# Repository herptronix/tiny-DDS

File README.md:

Tiny DDS
================

Open source (hardware & software) DDS generator, based on:
 - smart TFT module
 - AD9834
 - LM7171 fast amplifier

Small video: https://www.youtube.com/watch?v=Hllg0D2UqWg
Some explanations (french only): http://herptronix.blogspot.fr/2014/08/tiny-dds.html

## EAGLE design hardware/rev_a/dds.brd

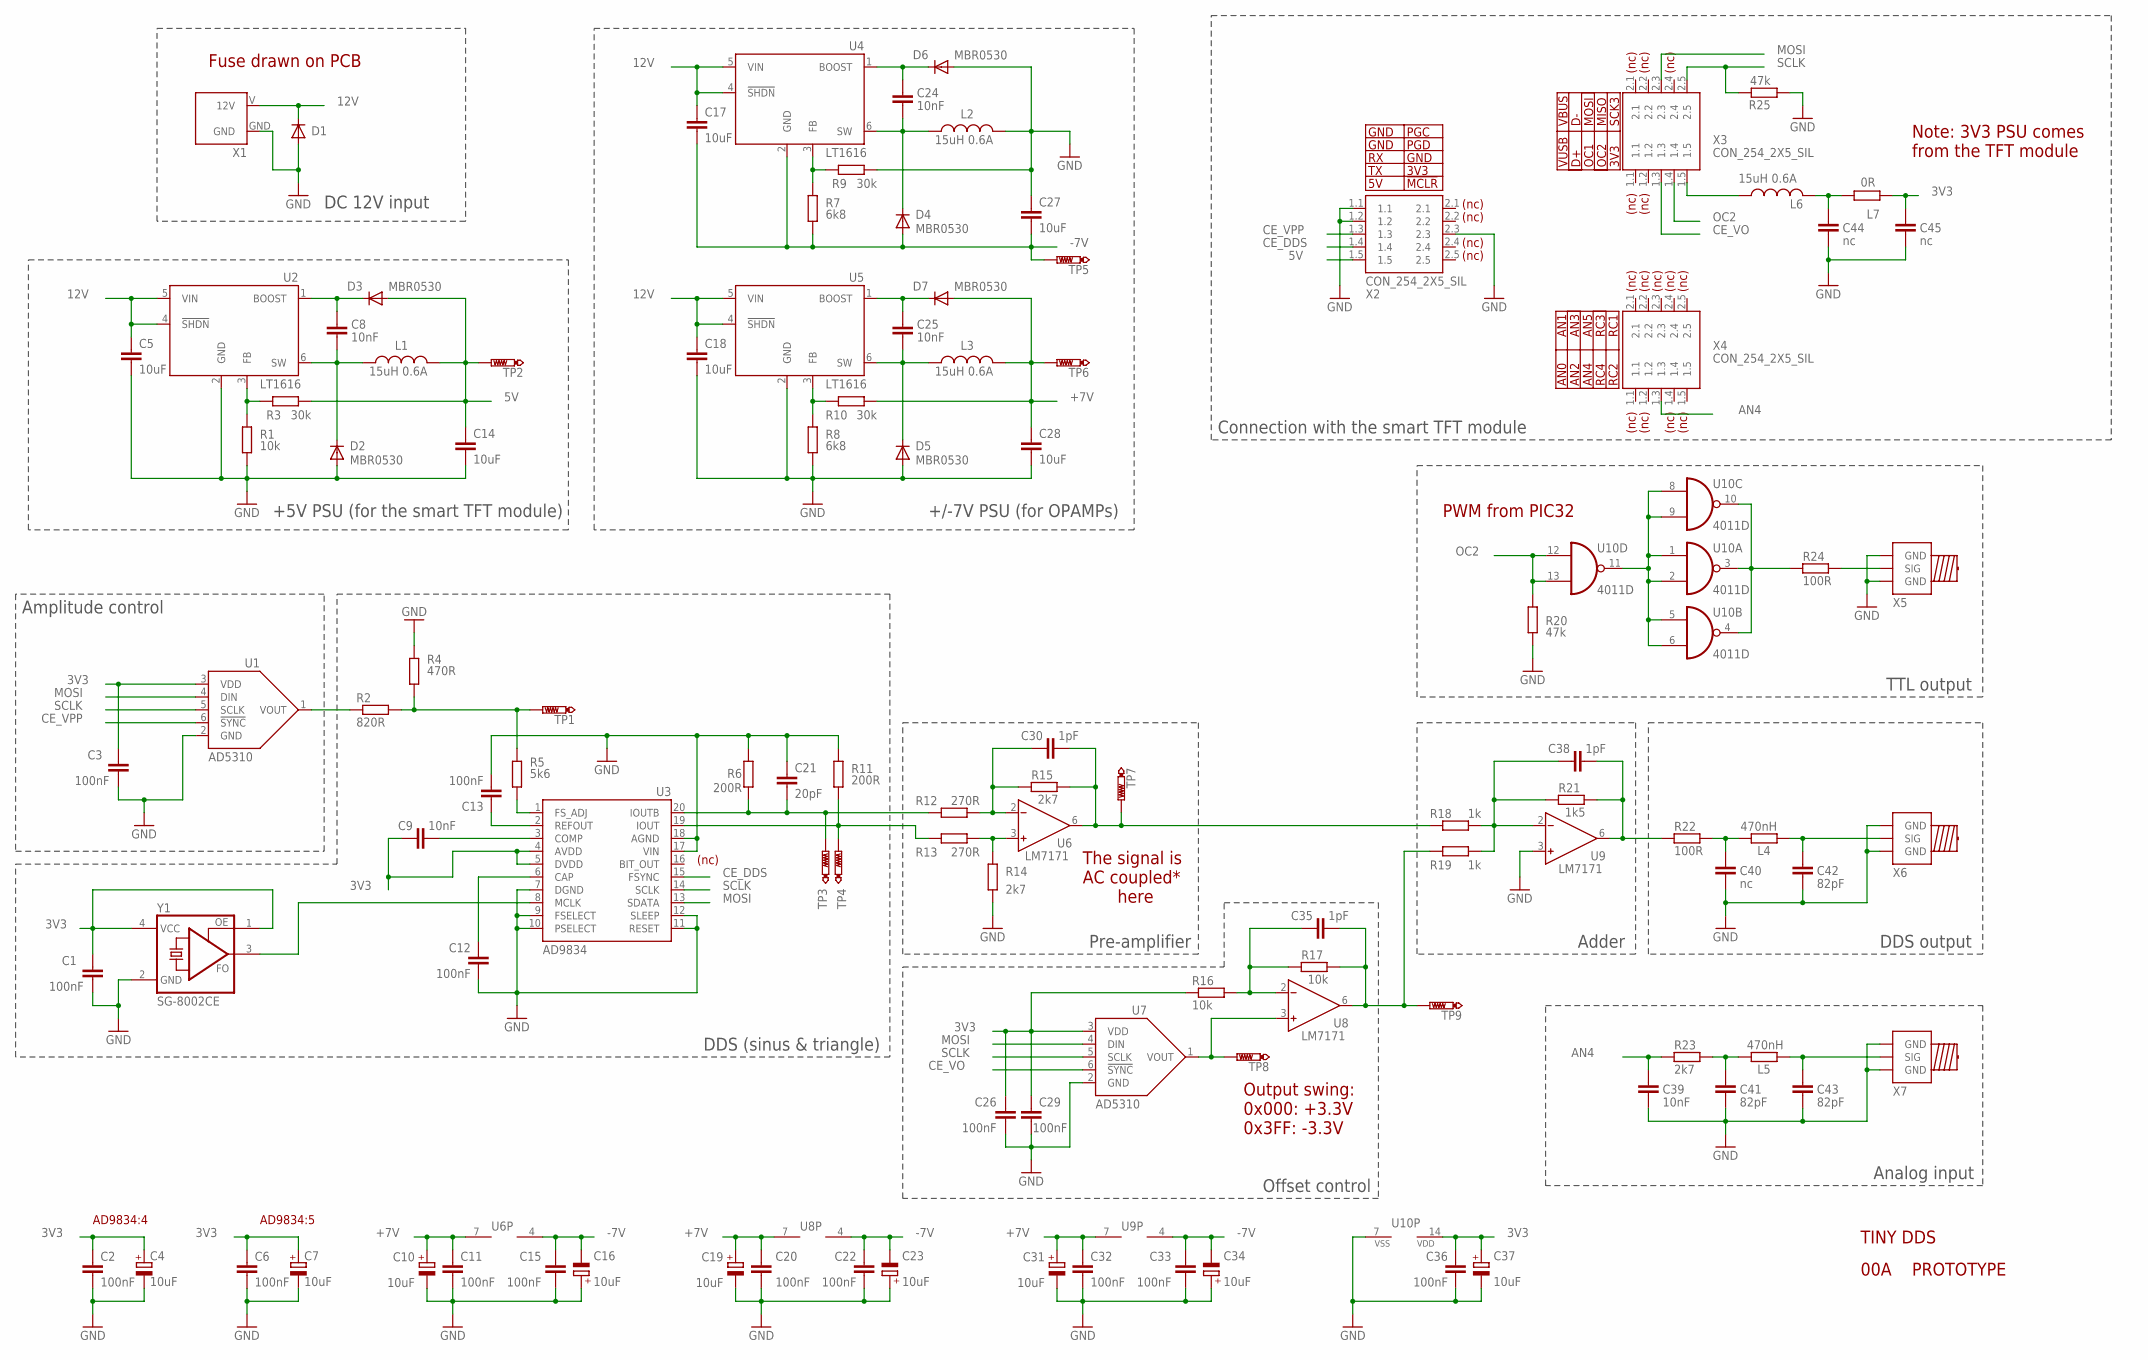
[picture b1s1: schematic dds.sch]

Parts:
C1, C2, C3, C6, C11, C12, C13, C15, C20, C22, C26, C29, C32, C33, C36: 100nF; C0603
C4, C7, C10, C16, C19, C23, C31, C34, C37: 10uF; SMC_B
C5, C14, C17, C18, C27, C28: 10uF; C0805
C8, C9, C24, C25, C39: 10nF; C0603
C21: 20pF; C0603
C30, C35, C38: 1pF; C0603
C40, C44, C45: nc; C0603
C41, C42, C43: 82pF; C0603
D1: DIODE-SMB; SMB
D2, D3, D4, D5, D6, D7: MBR0530; SOD123
L1, L2, L3, L6: 15uH 0.6A; L5X3
L4, L5: 470nH; R0603
L7: 0R; R0603
R1, R16, R17: 10k; R0603
R2: 820R; R0603
R3, R9, R10: 30k; R0603
R4: 470R; R0603
R5: 5k6; R0603
R6, R11: 200R; R0603
R7, R8: 6k8; R0603
R12, R13: 270R; R0603
R14, R15, R23: 2k7; R0603
R18, R19: 1k; R0603
R20, R25: 47k; R0603
R21: 1k5; R0603
R22, R24: 100R; R0603
TP1, TP2, TP3, TP4, TP5, TP6, TP7, TP8, TP9: PTR1B1,27; B1,27
U1, U7: AD5310; SOT23-6
U2, U4, U5: LT1616; SOT23-6
U3: AD9834; TSSOP20
U6, U9: LM7171; SO8
U8: LM7171; SO8; MPN AD811JRZ
U10: 4011D; SO14
X1: CON_12V
X2, X3, X4: CON_254_2X5_SIL; 2X5_SIL
X5, X6, X7: CON_SMA; SMA_SMD
Y1: SG-8002CE; ASF

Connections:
3V3: C1.1, C2.1, C3.1, C4.+, C6.1, C7.+, C9.2, C26.1, C29.1, C36.1, C37.+, C45.1, L7.2, R16.1, U1.3 (VDD), U3.4 (AVDD), U3.5 (DVDD), U7.3 (VDD), U10.14 (VDD), Y1.1 (OE), Y1.4 (VCC)
5V: C14.1, D3.A, L1.P$2, R3.1, TP2.TP, X2.1.5
12V: C5.1, C17.1, C18.1, D1.C, U2.4 (!SHDN), U2.5 (VIN), U4.4 (!SHDN), U4.5 (VIN), U5.4 (!SHDN), U5.5 (VIN), X1.V (12V)
+7V: C10.+, C11.1, C19.+, C20.1, C28.1, C31.+, C32.1, D7.A, L3.P$2, R10.1, TP6.TP, U6.7 (V+), U8.7 (V+), U9.7 (V+)
-7V: C15.1, C16.-, C17.2, C22.1, C23.-, C27.2, C33.1, C34.-, D4.A, R7.1, TP5.TP, U4.2 (GND), U6.4 (V-), U8.4 (V-), U9.4 (V-)
AN4: C39.1, R23.1, X4.1.3
CE_DDS: U3.15 (FSYNC), X2.1.4
CE_VO: U7.6 (!SYNC), X3.1.3
CE_VPP: U1.6 (!SYNC), X2.1.3
GND: C1.2, C2.2, C3.2, C4.-, C5.2, C6.2, C7.-, C10.-, C11.2, C12.2, C13.2, C14.2, C15.2, C16.+, C18.2, C19.-, C20.2, C21.1, C22.2, C23.+, C26.2, C27.1, C28.2, C29.2, C31.-, C32.2, C33.2, C34.+, C36.2, C37.-, C39.2, C40.2, C41.2, C42.2, C43.2, C44.2, C45.2, D1.A, D2.A, D5.A, D6.A, L2.P$2, R1.1, R4.1, R6.2, R8.1, R9.1, R11.2, R14.1, R20.1, R25.1, U1.2 (GND), U2.2 (GND), U3.7 (DGND), U3.9 (FSELECT), U3.10 (PSELECT), U3.11 (RESET), U3.12 (SLEEP), U3.17 (VIN), U3.18 (AGND), U5.2 (GND), U7.2 (GND), U9.3 (IN+), U10.7 (VSS), X1.GND, X2.1.1, X2.1.2, X2.2.3, X5.GND@1 (GND), X5.GND@2 (GND), X6.GND@1 (GND), X6.GND@2 (GND), X7.GND@1 (GND), X7.GND@2 (GND), Y1.2 (GND)
MOSI: U1.4 (DIN), U3.13 (SDATA), U7.4 (DIN), X3.2.3
unnamed: C21.2, R6.1, R12.1, TP3.TP, U3.20 (IOUTB)
unnamed: C13.1, U3.2 (REFOUT)
unnamed: C9.1, U3.3 (COMP)
unnamed: C8.1, D2.C, L1.P$1, U2.6 (SW)
unnamed: R11.1, R13.1, TP4.TP, U3.19 (IOUT)
unnamed: C12.1, U3.6 (CAP)
unnamed: U3.8 (MCLK), Y1.3 (FO)
unnamed: C30.1, R12.2, R15.1, U6.2 (IN-)
unnamed: R2.1, U1.1 (VOUT)
unnamed: C41.1, L5.1, R23.2
unnamed: R5.2, U3.1 (FS_ADJ)
unnamed: R13.2, R14.2, U6.3 (IN+)
unnamed: C30.2, R15.2, R18.1, TP7.TP, U6.6 (OUT)
unnamed: C40.1, L4.1, R22.2
unnamed: TP8.TP, U7.1 (VOUT), U8.3 (IN+)
unnamed: C35.1, R16.2, R17.1, U8.2 (IN-)
unnamed: C38.1, R18.2, R19.2, R21.1, U9.2 (IN-)
unnamed: C35.2, R17.2, R19.1, TP9.TP, U8.6 (OUT)
unnamed: C38.2, R21.2, R22.1, U9.6 (OUT)
unnamed: C8.2, D3.C, U2.1 (BOOST)
unnamed: C24.1, D4.C, L2.P$1, U4.6 (SW)
unnamed: C25.1, D5.C, L3.P$1, U5.6 (SW)
unnamed: R1.2, R3.2, U2.3 (FB)
unnamed: C25.2, D7.C, U5.1 (BOOST)
unnamed: R2.2, R4.2, R5.1, TP1.TP
unnamed: R8.2, R10.2, U5.3 (FB)
unnamed: C24.2, D6.C, U4.1 (BOOST)
unnamed: R7.2, R9.2, U4.3 (FB)
unnamed: C42.1, L4.2, X6.SIG
unnamed: C43.1, L5.2, X7.SIG
unnamed: U10.1 (I0), U10.2 (I1), U10.5 (I0), U10.6 (I1), U10.8 (I0), U10.9 (I1), U10.11 (O)
unnamed: R24.1, U10.3 (O), U10.4 (O), U10.10 (O)
unnamed: R24.2, X5.SIG
unnamed: C44.1, L6.P$2, L7.1
unnamed: L6.P$1, X3.1.5
OC2: R20.2, U10.12 (I0), U10.13 (I1), X3.1.4
SCLK: R25.2, U1.5 (SCLK), U3.14 (SCLK), U7.5 (SCLK), X3.2.5

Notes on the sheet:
PROTOTYPE
00A
TINY DDS
AD9834:4
AD9834:5
(nc)
GND
!MCLR
3V3
PGD
PGC
OC2
OC1
VUSB
SCK3
MISO
MOSI
VBUS
RC1
RC3
AN5
AN3
AN1
RC2
RC4
AN4
AN2
AN0
Connection with the smart TFT module
Note: 3V3 PSU comes
from the TFT module
TTL output
Analog input
Pre-amplifier
The signal is
AC coupled*
here
Offset control
Amplitude control
DDS output

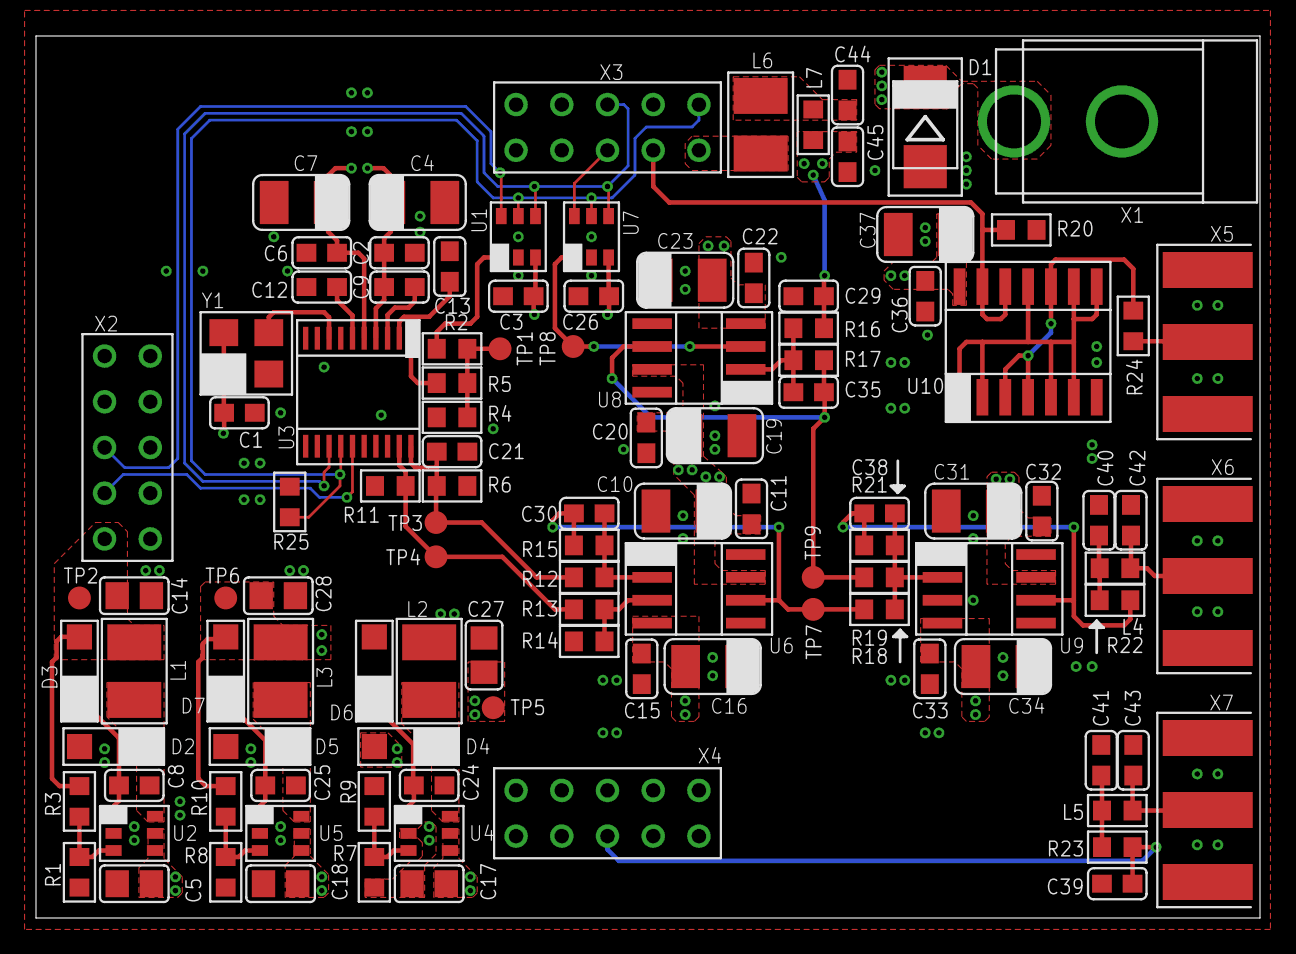
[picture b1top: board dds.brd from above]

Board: 2 copper layers, 68.0 x 49.0 mm, 111 parts (0 on the bottom side), 48 nets.

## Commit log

2014-09-13 Fist commit
